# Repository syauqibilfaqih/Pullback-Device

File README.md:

# Pullback-Device
This is an overview of a low-cost open source pullback device for varicose vein surgery.

## Usage
Look at the video attached bellow:
https://youtu.be/Uo2tgYB1XSM

## For Developers
1. Get the mechanical design at the folder "Mechanical" of this repository.
2. Get the schematic and PCB layout at the folder "Electrical" of this repository.
3. Get the source code by clonning this repository:
```
git clone https://github.com/syauqibilfaqih/Pullback-Device.git
```
Then, go to the folder "SourceCode". Make sure that you already have PlatformIO on your Visual Studio Code.

## Contact us
I realized that this readme still only contained short information right now. Should you have any question, don't hesitate to contact me at alisyauqibilfaqih@gmail.com

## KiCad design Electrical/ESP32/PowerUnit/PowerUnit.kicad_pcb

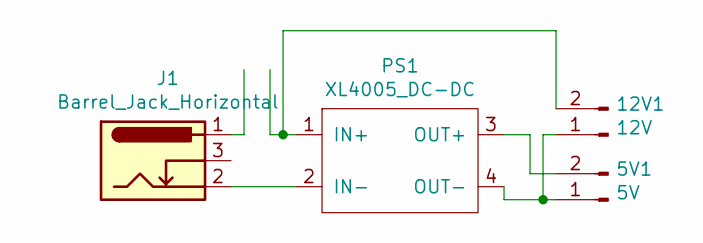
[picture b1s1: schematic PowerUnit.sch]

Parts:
5V1: 5V; Molex_KK-254_AE-6410-02A_1x02_P2.54mm_Vertical
12V1: 12V; Molex_KK-254_AE-6410-02A_1x02_P2.54mm_Vertical
J1: Barrel_Jack_Horizontal; BarrelJack_Horizontal
PS1: XL4005_DC-DC

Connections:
unnamed: 5V1.2, PS1.3 (OUT+)
unnamed: 5V1.1, 12V1.1, PS1.4 (OUT-)
unnamed: 12V1.2, PS1.1 (IN+)
unnamed: J1.2, PS1.2 (IN-)

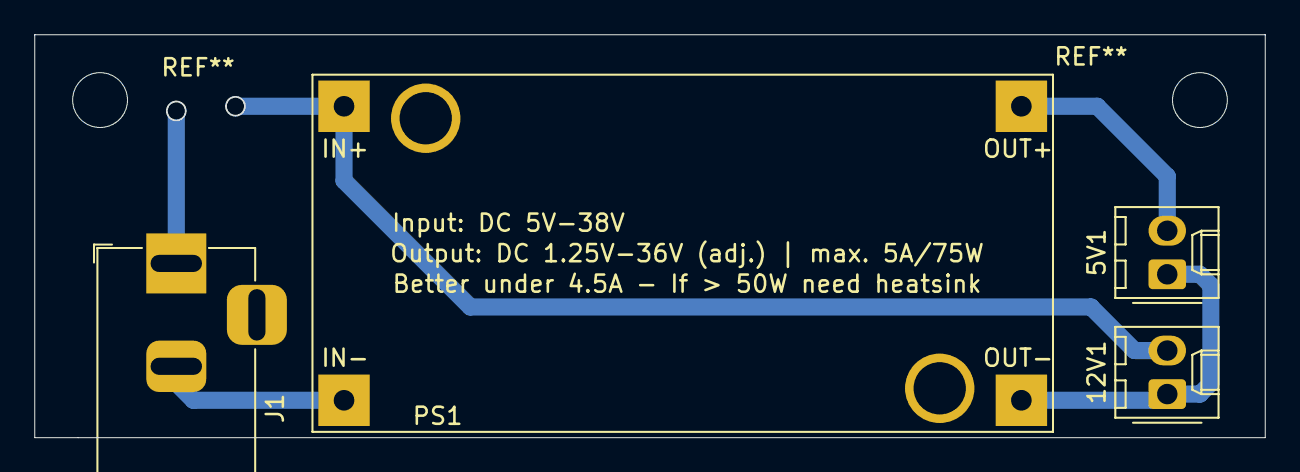
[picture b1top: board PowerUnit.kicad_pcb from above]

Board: 2 copper layers, 71.8 x 23.5 mm, 4 parts (0 on the bottom side), 4 nets.

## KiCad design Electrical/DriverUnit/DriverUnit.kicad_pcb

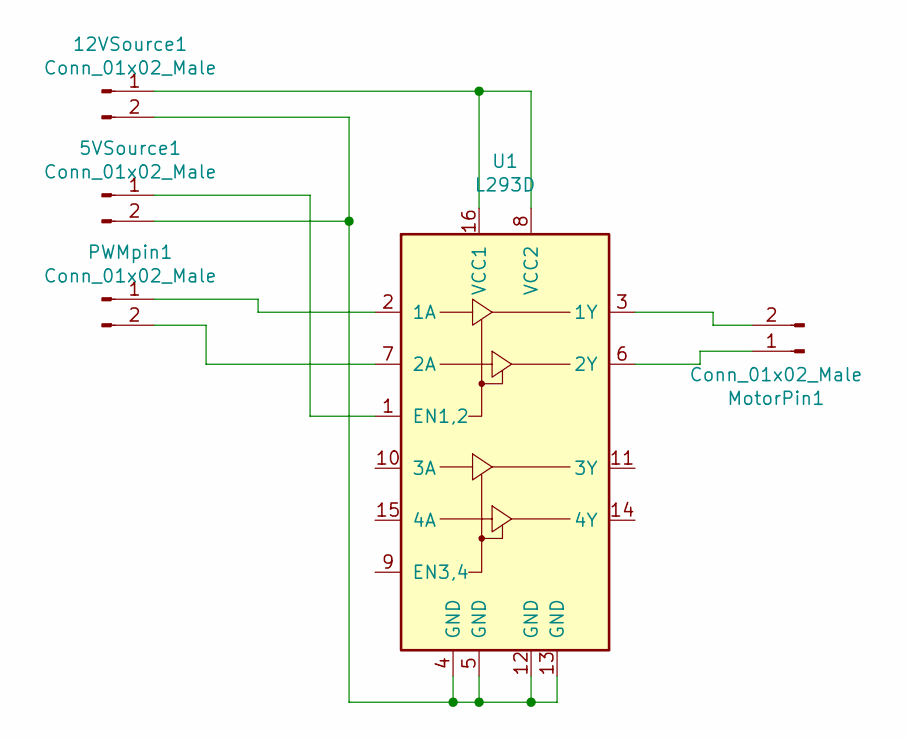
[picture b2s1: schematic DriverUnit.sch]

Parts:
5VSource1, 12VSource1: Conn_01x02_Male; Molex_KK-254_AE-6410-02A_1x02_P2.54mm_Vertical
MotorPin1: Conn_01x02_Male; Molex_KK-254_AE-6410-02A_1x02_P2.54mm_Vertical
PWMpin1: Conn_01x02_Male; Molex_KK-254_AE-6410-02A_1x02_P2.54mm_Vertical
U1: L293D; DIP-16_W7.62mm

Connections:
unnamed: 5VSource1.1, U1.1 (EN1,2)
unnamed: 12VSource1.1, U1.8 (VCC2), U1.16 (VCC1)
unnamed: 5VSource1.2, 12VSource1.2, U1.4 (GND), U1.5 (GND), U1.12 (GND), U1.13 (GND)
unnamed: MotorPin1.1, U1.6 (2Y)
unnamed: MotorPin1.2, U1.3 (1Y)
unnamed: PWMpin1.1, U1.2 (1A)
unnamed: PWMpin1.2, U1.7 (2A)

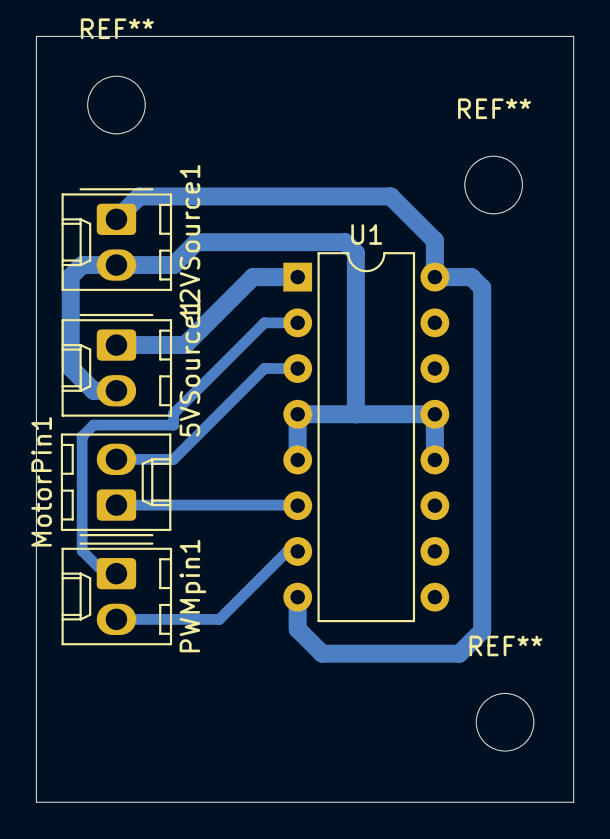
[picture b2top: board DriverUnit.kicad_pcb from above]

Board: 2 copper layers, 29.8 x 42.5 mm, 5 parts (0 on the bottom side), 7 nets.

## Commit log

2024-01-19 Fix project foldering
2024-01-19 Deleted source code outside
2024-01-19 Create LICENSE
2024-08-21 Added ESP32Encoder Library
2024-08-21 Chaces kicad
2024-08-21 Implemented OTA to the firmware
2024-08-21 Changed upload method
2024-08-30 Added encoder initialization
2024-08-30 Chaces
